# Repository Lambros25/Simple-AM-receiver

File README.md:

# Simple AM Radio Receiver

## Goal
This was originally a project through university, so the schematic was given. The project however was aiming at making the main circuit without the volume bar and soldering it on a perfboard.

PCB was optional but a great learning curve.

## PCB Design Choices

### Transformer
     The only difference from the intended schematic is the transformer shape. It was meant to be wrapped outside the core and about 6 turns on the primary and 60 on the secondary, however I felt like the losses would be too great to achieve oscillation at 729kHz with a 30pf-60pf capacitor. Thus I instead did 2 and 21 turns inside the core taking advantage fully of the magnetic flux.
    
    This turned out to be a great decision as we had no amplitude issues when testing.

### Ground plane and Connector location
    A solid ground plane (2nd layer) was the best move to keep noise to a minimum with the exception of the area below the inductor, where parasitic capacitance would decalibrate our oscillation. The 1st layer was also mostly ground for shielding reasons. Finally, the ground connector was placed in the middle in order to essentialy block digital ground (from the LEDs) from reaching the more sensitive signal area.

    In minimal testing this showed up to be a correct decision as grounding from the input area resulted in audible *pops* when the LEDs were switching.

### +V Plane
    At the right side, in the "digital" area, many connectors as well as the LEDs required VCC, this was easily solved by adding a +V plane on the first layer of the PCB, resulting in a low resistance clean path for every component to get power. Signal in that area was not going to be audible and was not sensitive, as such, noise reduction was not a number 1 priority.

## Errors

### IC Pin 9
    Due to the +V plane, an island was left that floated and blocked Pin 9 of the LM3915 IC. This was a serious overlook but thankfully not a catastrophic error. The IC pin worked like it was grounded giving a volume "indicator" instead of a full volume bar.

### Abscence of Test Points
     Made the assembly and testing really hard and stressful without cause.

## Improvements

### Size
    Compacting the whole board would be greatly beneficial for size. AF isn't so sensitive so it wouldn't make a big difference but cost would be less.

### Redundancy 
    No need for ground (-) input.

## Overview
    For a first PCB looked pretty good and worked spectacularly.

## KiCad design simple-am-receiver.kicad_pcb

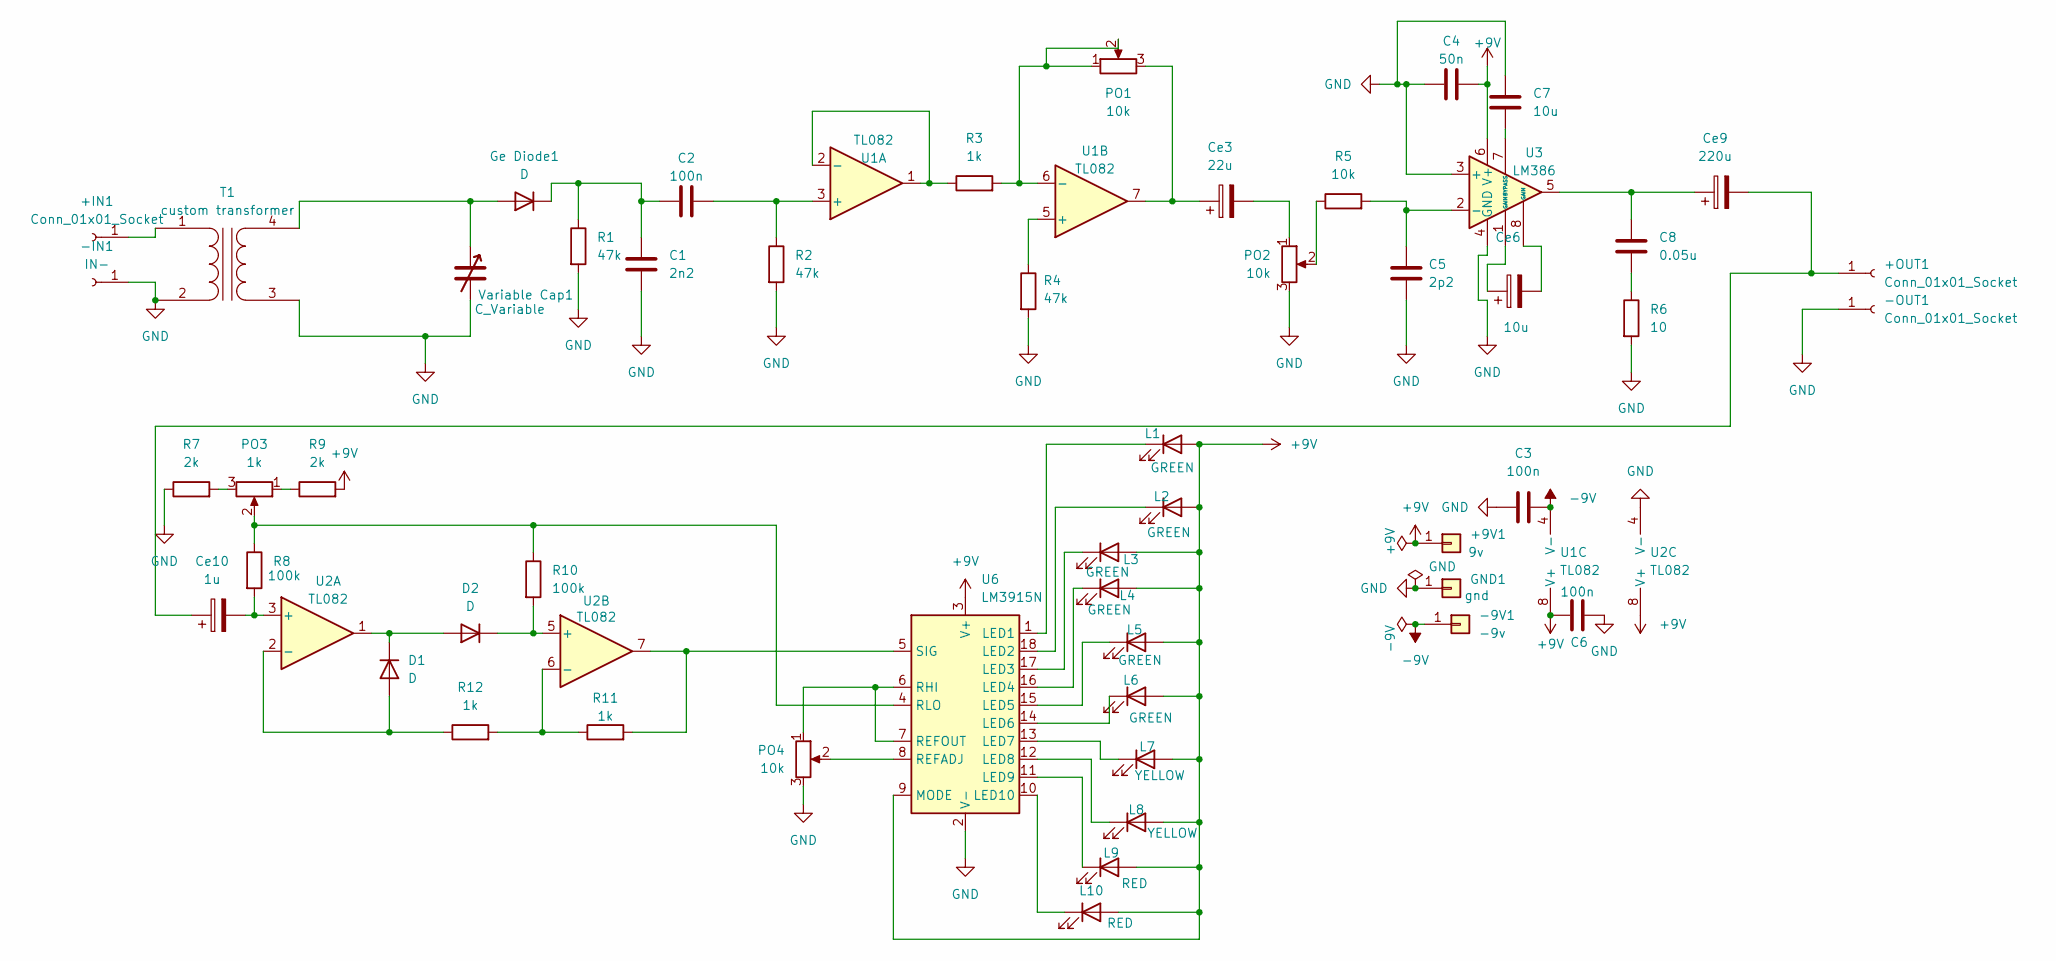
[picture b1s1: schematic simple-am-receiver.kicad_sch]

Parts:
+9V1: 9v; Banana_Jack_1Pin
+IN1: Conn_01x01_Socket; PinSocket_1x01_P1.27mm_Vertical
+OUT1: Conn_01x01_Socket; PinHeader_1x01_P1.00mm_Vertical
-9V1: -9v; Banana_Jack_1Pin
-IN1: IN-; PinSocket_1x01_P1.27mm_Vertical
-OUT1: Conn_01x01_Socket; PinHeader_1x01_P1.00mm_Vertical
C1: 2n2; C_Disc_D5.0mm_W2.5mm_P2.50mm
C2, C3, C6: 100n; C_Disc_D5.0mm_W2.5mm_P2.50mm
C4: 50n; C_Disc_D5.0mm_W2.5mm_P2.50mm
C5: 2p2; C_Disc_D5.0mm_W2.5mm_P2.50mm
C7: 10u; C_Disc_D5.0mm_W2.5mm_P2.50mm
C8: 0.05u; C_Disc_D5.0mm_W2.5mm_P2.50mm
Ce3: 22u; CP_Radial_D5.0mm_P2.00mm
Ce6: 10u; CP_Radial_D5.0mm_P2.00mm
Ce9: 220u; CP_Radial_D6.3mm_P2.50mm
Ce10: 1u; CP_Radial_D4.0mm_P1.50mm
D1, D2: D; D_DO-41_SOD81_P7.62mm_Horizontal
GND1: gnd; Banana_Jack_1Pin
Ge Diode1: D; D_DO-35_SOD27_P7.62mm_Horizontal
L1, L2, L3, L4, L5, L6: GREEN; LED_D5.0mm
L7, L8: YELLOW; LED_D5.0mm
L9, L10: RED; LED_D5.0mm
PO1, PO2, PO4: 10k; Potentiometer_Alps_RK09K_Single_Vertical
PO3: 1k; Potentiometer_Alps_RK09K_Single_Vertical
R1, R2, R4: 47k; R_Axial_DIN0207_L6.3mm_D2.5mm_P7.62mm_Horizontal
R3, R11, R12: 1k; R_Axial_DIN0207_L6.3mm_D2.5mm_P7.62mm_Horizontal
R5: 10k; R_Axial_DIN0207_L6.3mm_D2.5mm_P7.62mm_Horizontal
R6: 10; R_Axial_DIN0309_L9.0mm_D3.2mm_P12.70mm_Horizontal
R7, R9: 2k; R_Axial_DIN0207_L6.3mm_D2.5mm_P7.62mm_Horizontal
R8, R10: 100k; R_Axial_DIN0207_L6.3mm_D2.5mm_P7.62mm_Horizontal
T1: custom transformer; Transformer
U1, U2: TL082; DIP-8_W7.62mm
U3: LM386; DIP-8_W7.62mm
U6: LM3915N; DIP-18_W7.62mm
Variable Cap1: C_Variable; Variable Capacitor

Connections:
+9V: +9V1.1, C4.2, C6.1, L1.2 (A), L2.2 (A), L3.2 (A), L4.2 (A), L5.2 (A), L6.2 (A), L7.2 (A), L8.2 (A), L9.2 (A), L10.2 (A), R9.2, U1.8 (V+), U2.8 (V+), U3.6 (V+), U6.3 (V+), U6.9 (MODE)
-9V: -9V1.1, C3.2, U1.4 (V-)
GND: -IN1.1, -OUT1.1, C1.1, C3.1, C4.1, C5.2, C6.2, C7.1, GND1.1, PO2.3, PO4.3, R1.2, R2.2, R4.2, R6.2, R7.1, T1.2 (AB), T1.3 (SA), U2.4 (V-), U3.3 (+), U3.4 (GND), U6.2 (V-), Variable Cap1.2
unnamed: +IN1.1, T1.1 (AA)
unnamed: +OUT1.1, Ce9.2, Ce10.1
unnamed: C8.1, Ce9.1, U3.5
unnamed: C8.2, R6.1
unnamed: Ce3.1, PO1.3, U1.7
unnamed: Ce3.2, PO2.1
unnamed: Ce6.1, U3.1 (GAIN)
unnamed: Ce6.2, U3.8 (GAIN)
unnamed: D1.2 (A), R12.1, U2.2 (-)
unnamed: D1.1 (K), D2.2 (A), U2.1
unnamed: D2.1 (K), R10.2, U2.5 (+)
unnamed: Ge Diode1.2 (A), T1.4 (SB), Variable Cap1.1
unnamed: C1.2, C2.1, Ge Diode1.1 (K), R1.1
unnamed: L1.1 (K), U6.1 (LED1)
unnamed: L2.1 (K), U6.18 (LED2)
unnamed: L3.1 (K), U6.17 (LED3)
unnamed: L4.1 (K), U6.16 (LED4)
unnamed: L5.1 (K), U6.15 (LED5)
unnamed: L6.1 (K), U6.14 (LED6)
unnamed: L7.1 (K), U6.13 (LED7)
unnamed: L8.1 (K), U6.12 (LED8)
unnamed: L9.1 (K), U6.11 (LED9)
unnamed: L10.1 (K), U6.10 (LED10)
unnamed: PO2.2, R5.1
unnamed: PO3.1, R9.1
unnamed: PO3.3, R7.2
unnamed: C2.2, R2.1, U1.3 (+)
unnamed: R3.1, U1.1, U1.2 (-)
unnamed: R4.1, U1.5 (+)
unnamed: PO1.1, PO1.2, R3.2, U1.6 (-)
unnamed: Ce10.2, R8.2, U2.3 (+)
unnamed: R11.1, R12.2, U2.6 (-)
unnamed: C5.1, R5.2, U3.2 (-)
unnamed: C7.2, U3.7 (BYPASS)
unnamed: PO4.2, U6.8 (REFADJ)
unnamed: PO4.1, U6.6 (RHI), U6.7 (REFOUT)
unnamed: PO3.2, R8.1, R10.1, U6.4 (RLO)
unnamed: R11.2, U2.7, U6.5 (SIG)

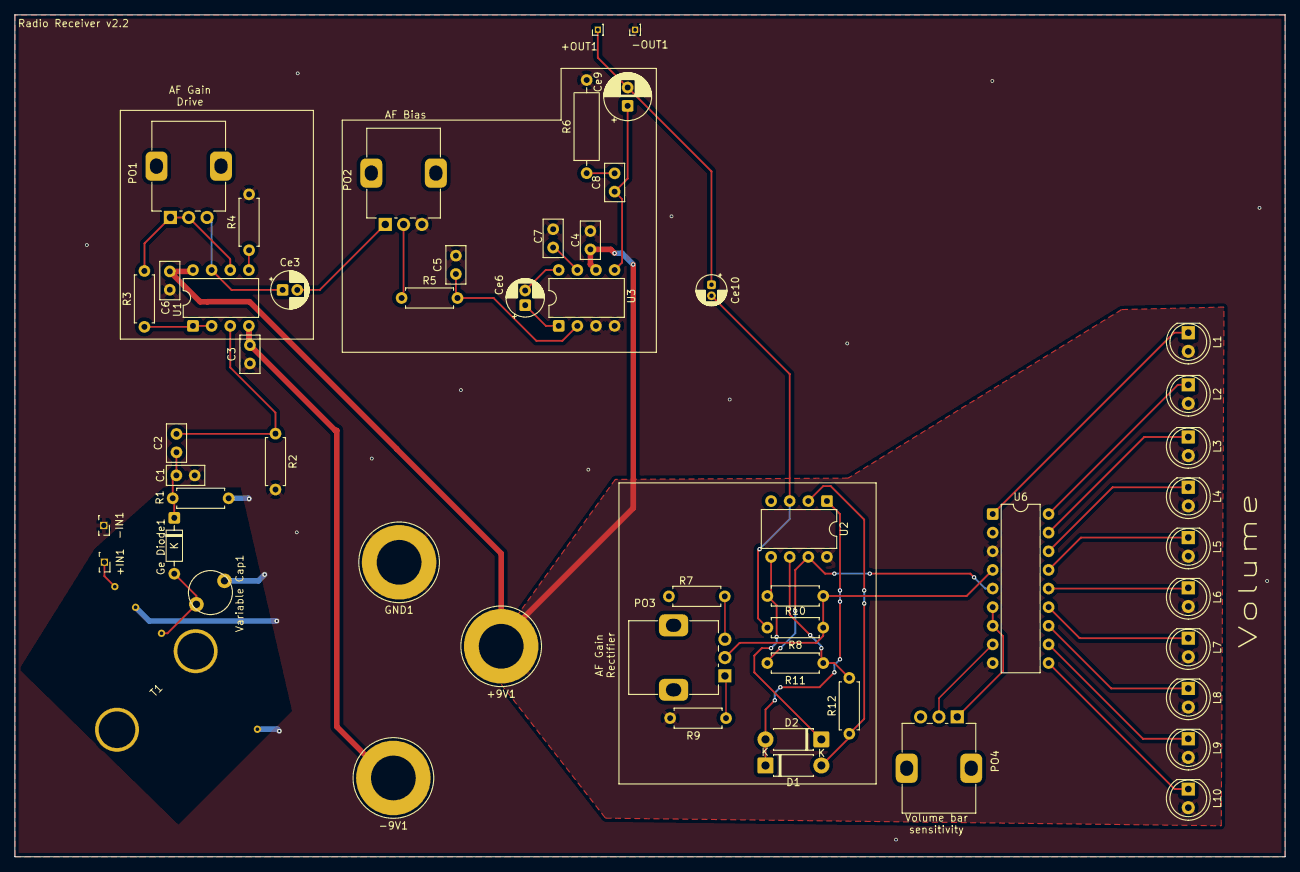
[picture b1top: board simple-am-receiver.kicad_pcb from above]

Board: 2 copper layers, 173.2 x 114.8 mm, 54 parts (0 on the bottom side), 41 nets.

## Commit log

2026-02-28 added files
2026-02-28 Added README. Project is finished
